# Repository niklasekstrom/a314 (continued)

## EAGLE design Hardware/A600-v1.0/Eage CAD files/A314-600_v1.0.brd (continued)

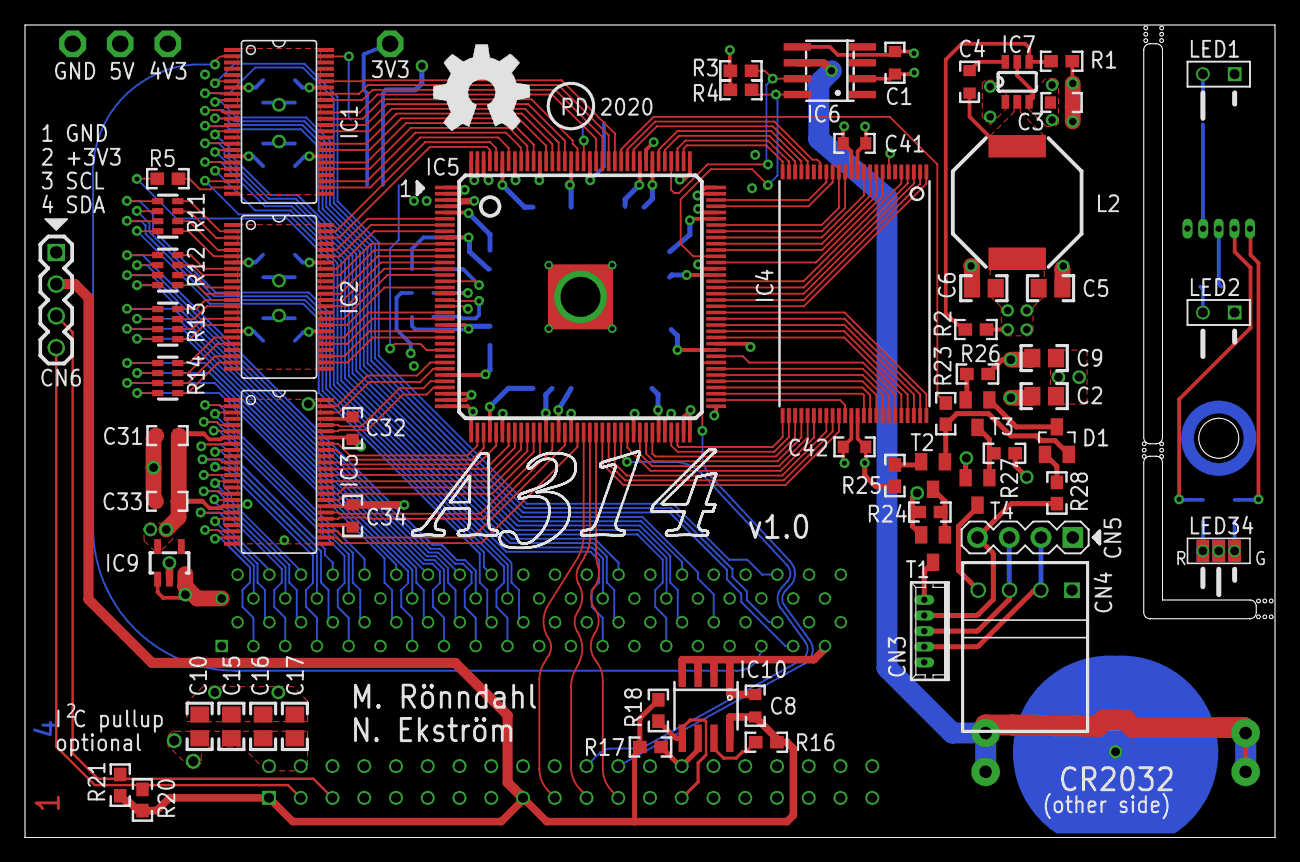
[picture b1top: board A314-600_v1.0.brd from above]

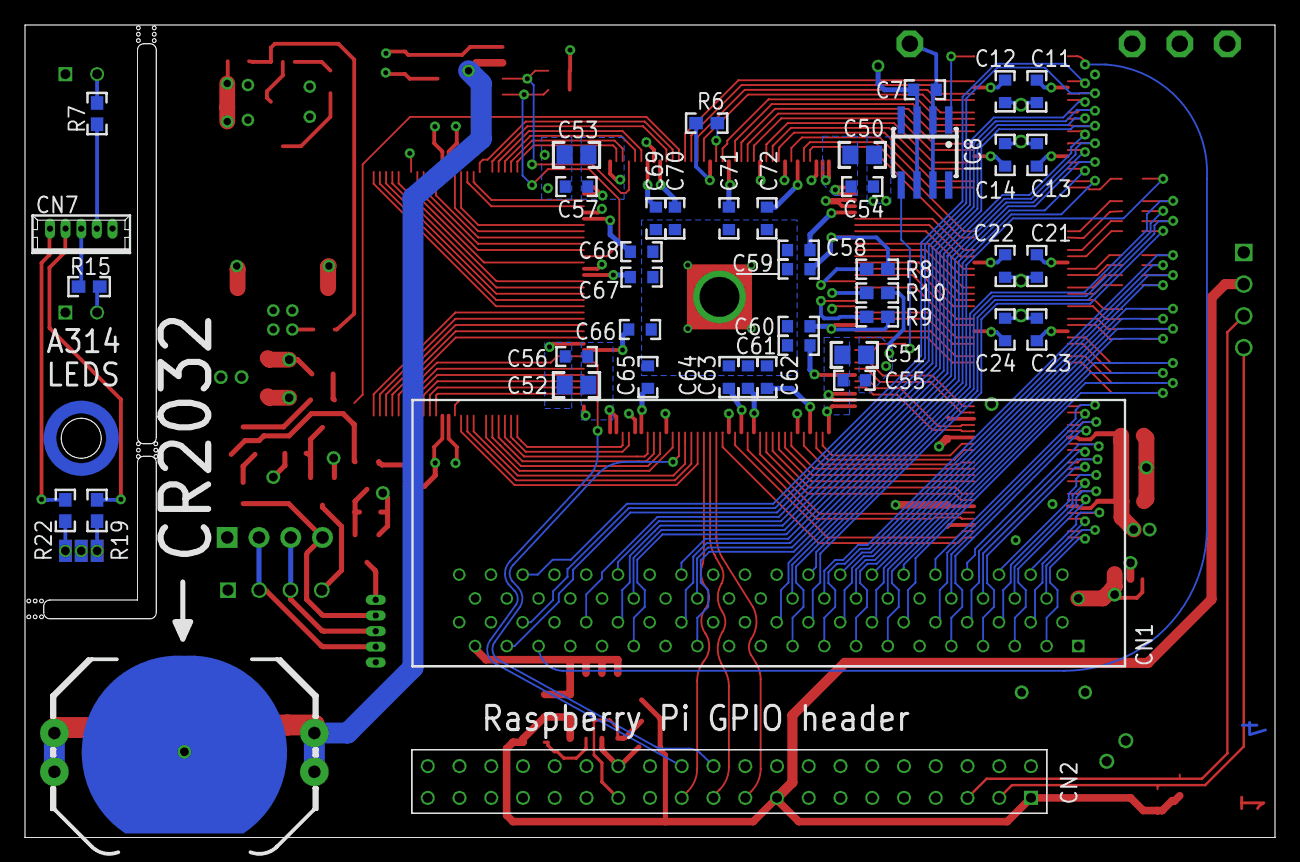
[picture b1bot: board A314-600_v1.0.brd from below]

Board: 4 copper layers, 100.0 x 65.0 mm, 111 parts (43 on the bottom side), 197 nets.

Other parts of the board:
U$1: OSHW_8_NOTEXT
U$2: A314_LOGO

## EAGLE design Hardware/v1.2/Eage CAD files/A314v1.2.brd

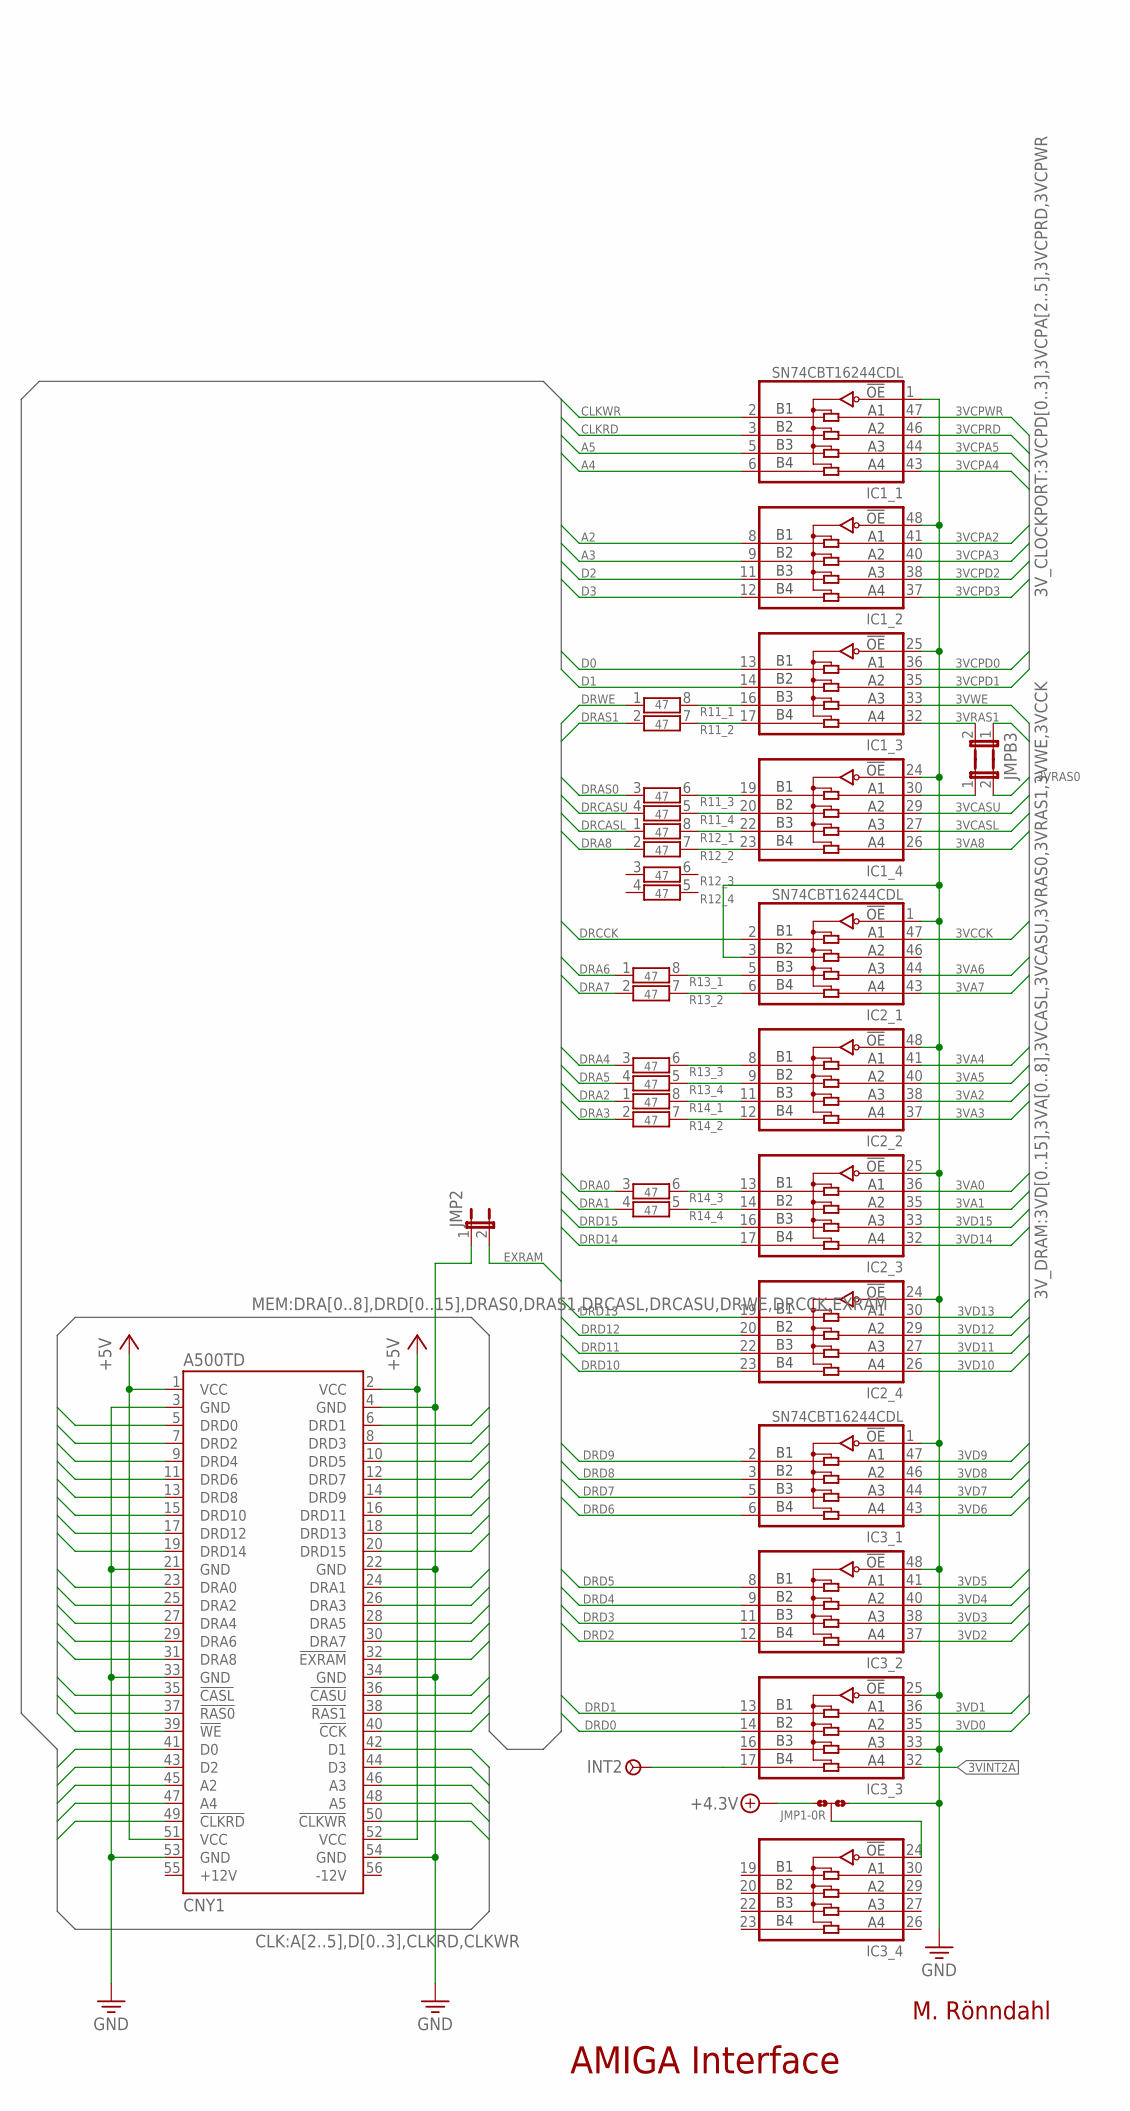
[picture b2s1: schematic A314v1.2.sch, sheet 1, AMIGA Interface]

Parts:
CNY1: A500TD; TRAPDOOR
IC1, IC2, IC3: SN74CBT16244CDL; SSOP-DL48
INT2: TP1; P1-08
JMP1: 0R-JUMPC; C0R-JMP
JMP2: JP1E; JP1
JMP3: RAS0; JP1
JMPB3: JP1E; JP1
R11, R12, R13, R14: 47; CTS742C083

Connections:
3VA0: IC2.36 (A1); also elsewhere on the board
3VA1: IC2.35 (A2); also elsewhere on the board
3VA2: IC2.38 (A3); also elsewhere on the board
3VA3: IC2.37 (A4); also elsewhere on the board
3VA4: IC2.41 (A1); also elsewhere on the board
3VA5: IC2.40 (A2); also elsewhere on the board
3VA6: IC2.44 (A3); also elsewhere on the board
3VA7: IC2.43 (A4); also elsewhere on the board
3VA8: IC1.26 (A4); also elsewhere on the board
3VCASL: IC1.27 (A3); also elsewhere on the board
3VCASU: IC1.29 (A2); also elsewhere on the board
3VCCK: IC2.47 (A1); also elsewhere on the board
3VCPA2: IC1.41 (A1); also elsewhere on the board
3VCPA3: IC1.40 (A2); also elsewhere on the board
3VCPA4: IC1.43 (A4); also elsewhere on the board
3VCPA5: IC1.44 (A3); also elsewhere on the board
3VCPD0: IC1.36 (A1); also elsewhere on the board
3VCPD1: IC1.35 (A2); also elsewhere on the board
3VCPD2: IC1.38 (A3); also elsewhere on the board
3VCPD3: IC1.37 (A4); also elsewhere on the board
3VCPRD: IC1.46 (A2); also elsewhere on the board
3VCPWR: IC1.47 (A1); also elsewhere on the board
3VD0: IC3.35 (A2); also elsewhere on the board
3VD1: IC3.36 (A1); also elsewhere on the board
3VD2: IC3.37 (A4); also elsewhere on the board
3VD3: IC3.38 (A3); also elsewhere on the board
3VD4: IC3.40 (A2); also elsewhere on the board
3VD5: IC3.41 (A1); also elsewhere on the board
3VD6: IC3.43 (A4); also elsewhere on the board
3VD7: IC3.44 (A3); also elsewhere on the board
3VD8: IC3.46 (A2); also elsewhere on the board
3VD9: IC3.47 (A1); also elsewhere on the board
3VD10: IC2.26 (A4); also elsewhere on the board
3VD11: IC2.27 (A3); also elsewhere on the board
3VD12: IC2.29 (A2); also elsewhere on the board
3VD13: IC2.30 (A1); also elsewhere on the board
3VD14: IC2.32 (A4); also elsewhere on the board
3VD15: IC2.33 (A3); also elsewhere on the board
3VINT2A: IC3.32 (A4); also elsewhere on the board
3VRAS0: JMP3.2; also elsewhere on the board
3VRAS1: JMPB3.1; also elsewhere on the board
3VWE: IC1.33 (A3); also elsewhere on the board
+4.3V: JMP1.1; also elsewhere on the board
+5V: CNY1.1 (VCC), CNY1.2 (VCC), CNY1.51 (VCC), CNY1.52 (VCC); also elsewhere on the board
A2: CNY1.45 (A2), IC1.8 (B1)
A3: CNY1.46 (A3), IC1.9 (B2)
A4: CNY1.47 (A4), IC1.6 (B4)
A5: CNY1.48 (A5), IC1.5 (B3)
CLKRD: CNY1.49 (!CLKRD), IC1.3 (B2)
CLKWR: CNY1.50 (!CLKWR), IC1.2 (B1)
D0: CNY1.41 (D0), IC1.13 (B1)
D1: CNY1.42 (D1), IC1.14 (B2)
D2: CNY1.43 (D2), IC1.11 (B3)
D3: CNY1.44 (D3), IC1.12 (B4)
DRA0: CNY1.23 (DRA0), R14.3
DRA1: CNY1.24 (DRA1), R14.4
DRA2: CNY1.25 (DRA2), R14.1
DRA3: CNY1.26 (DRA3), R14.2
DRA4: CNY1.27 (DRA4), R13.3
DRA5: CNY1.28 (DRA5), R13.4
DRA6: CNY1.29 (DRA6), R13.1
DRA7: CNY1.30 (DRA7), R13.2
DRA8: CNY1.31 (DRA8), R12.2
DRA8_L: IC1.23 (B4), R12.7
DRAS0: CNY1.37 (!RAS0), R11.3
DRAS0_L: IC1.19 (B1), R11.6
DRAS1: CNY1.38 (!RAS1), R11.2
DRAS1_L: IC1.17 (B4), R11.7
DRCASL: CNY1.35 (!CASL), R12.1
DRCASL_L: IC1.22 (B3), R12.8
DRCASU: CNY1.36 (!CASU), R11.4
DRCASU_L: IC1.20 (B2), R11.5
DRCCK: CNY1.40 (!CCK), IC2.2 (B1)
DRD0: CNY1.5 (DRD0), IC3.14 (B2)
DRD1: CNY1.6 (DRD1), IC3.13 (B1)
DRD2: CNY1.7 (DRD2), IC3.12 (B4)
DRD3: CNY1.8 (DRD3), IC3.11 (B3)
DRD4: CNY1.9 (DRD4), IC3.9 (B2)
DRD5: CNY1.10 (DRD5), IC3.8 (B1)
DRD6: CNY1.11 (DRD6), IC3.6 (B4)
DRD7: CNY1.12 (DRD7), IC3.5 (B3)
DRD8: CNY1.13 (DRD8), IC3.3 (B2)
DRD9: CNY1.14 (DRD9), IC3.2 (B1)
DRD10: CNY1.15 (DRD10), IC2.23 (B4)
DRD11: CNY1.16 (DRD11), IC2.22 (B3)
DRD12: CNY1.17 (DRD12), IC2.20 (B2)
DRD13: CNY1.18 (DRD13), IC2.19 (B1)
DRD14: CNY1.19 (DRD14), IC2.17 (B4)
DRD15: CNY1.20 (DRD15), IC2.16 (B3)
DRWE: CNY1.39 (!WE), R11.1
DRWE_L: IC1.16 (B3), R11.8
EXRAM: CNY1.32 (!EXRAM), JMP2.2
GND: CNY1.3 (GND), CNY1.4 (GND), CNY1.21 (GND), CNY1.22 (GND), CNY1.33 (GND), CNY1.34 (GND), CNY1.53 (GND), CNY1.54 (GND), IC1.1 (!OE), IC1.24 (!OE), IC1.25 (!OE), IC1.48 (!OE), IC2.1 (!OE), IC2.3 (B2), IC2.24 (!OE), IC2.25 (!OE), IC2.48 (!OE), IC3.1 (!OE), IC3.25 (!OE), IC3.33 (A3), IC3.48 (!OE), JMP1.3, JMP2.1; also elsewhere on the board
INT2A: IC3.17 (B4), INT2.TP
unnamed: IC2.14 (B2), R14.5
unnamed: IC2.13 (B1), R14.6
unnamed: IC2.12 (B4), R14.7
unnamed: IC2.11 (B3), R14.8
unnamed: IC2.9 (B2), R13.5
unnamed: IC2.8 (B1), R13.6
unnamed: IC2.6 (B4), R13.7
unnamed: IC2.5 (B3), R13.8
OUTPUT_EN: IC3.24 (!OE), JMP1.2
RAS0: IC1.30 (A1), JMP3.1
RAS1: IC1.32 (A4), JMPB3.2

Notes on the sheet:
AMIGA Interface
M. Rönndahl

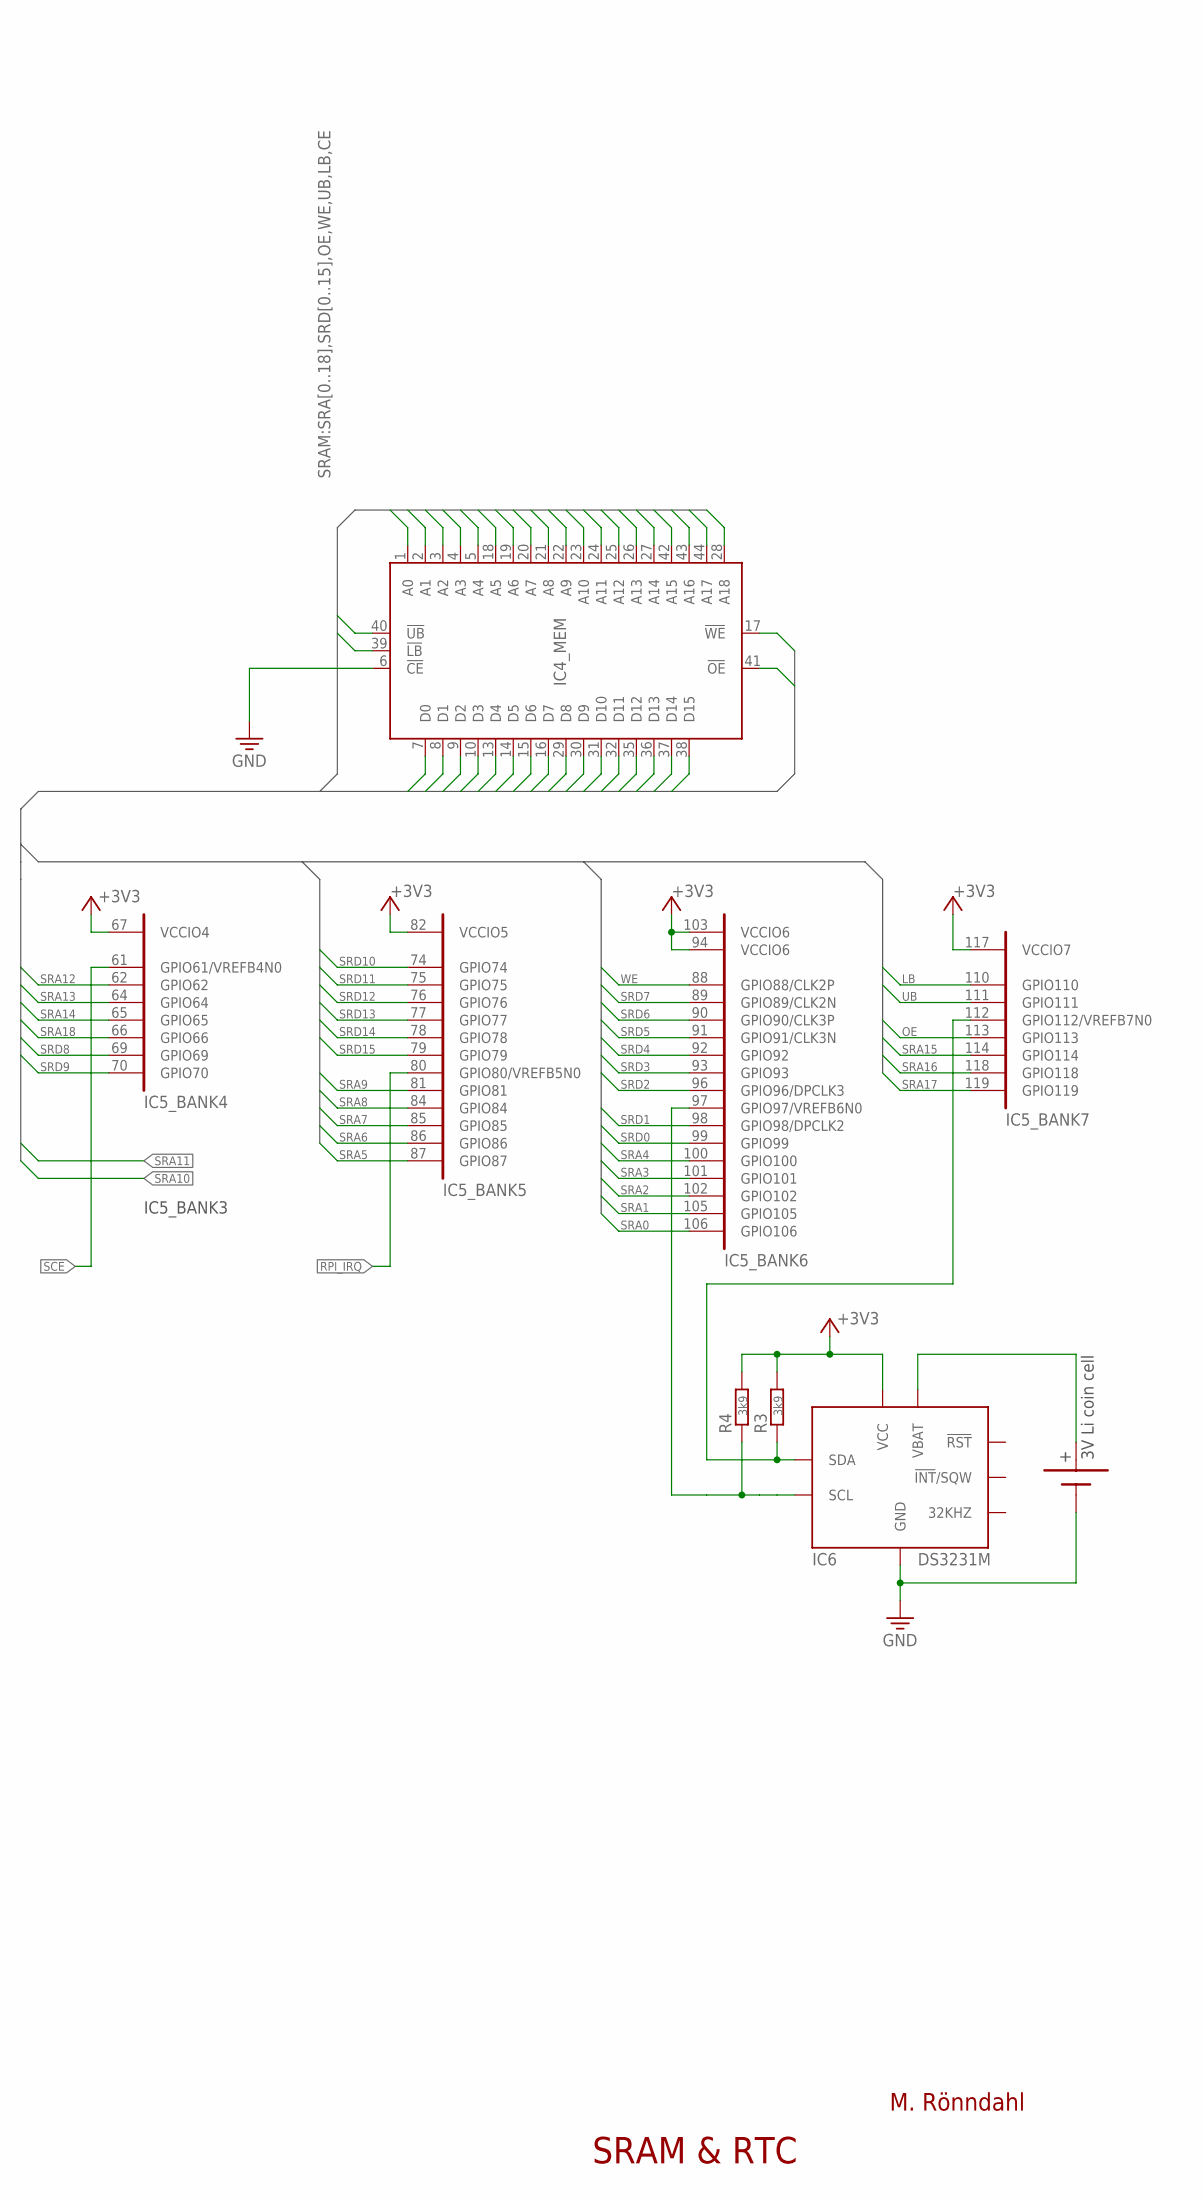
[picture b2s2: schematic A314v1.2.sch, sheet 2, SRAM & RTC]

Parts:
BAT1: CR2025/CR2032TH; LINX20XX-THM
IC4: IS61WV51216BLL-10TLI; TSOP-2
IC5: 10M08SCE144; SQFP-S-20X20-144
IC6: DS3231M; SOIC8
R3, R4: 3k9; R0805

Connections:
+: BAT1.+@1 (+), BAT1.+@2 (+), BAT1.+@3 (+), BAT1.+@4 (+), IC6.6 (VBAT)
+3V3: IC5.67 (VCCIO4), IC5.82 (VCCIO5), IC5.94 (VCCIO6), IC5.103 (VCCIO6), IC5.117 (VCCIO7), IC6.2 (VCC), R3.2, R4.2; also elsewhere on the board
GND: BAT1.GND (-), IC4.6 (!CE), IC6.5 (GND); also elsewhere on the board
LB: IC4.39 (!LB), IC5.110 (GPIO110)
OE: IC4.41 (!OE), IC5.113 (GPIO113)
RPI_IRQ: IC5.80 (GPIO80/VREFB5N0); also elsewhere on the board
SCE: IC5.61 (GPIO61/VREFB4N0); also elsewhere on the board
SCL: IC5.97 (GPIO97/VREFB6N0), IC6.8 (SCL), R4.1
SDA: IC5.112 (GPIO112/VREFB7N0), IC6.7 (SDA), R3.1
SRA0: IC4.1 (A0), IC5.106 (GPIO106)
SRA1: IC4.2 (A1), IC5.105 (GPIO105)
SRA2: IC4.3 (A2), IC5.102 (GPIO102)
SRA3: IC4.4 (A3), IC5.101 (GPIO101)
SRA4: IC4.5 (A4), IC5.100 (GPIO100)
SRA5: IC4.18 (A5), IC5.87 (GPIO87)
SRA6: IC4.19 (A6), IC5.86 (GPIO86)
SRA7: IC4.20 (A7), IC5.85 (GPIO85)
SRA8: IC4.21 (A8), IC5.84 (GPIO84)
SRA9: IC4.22 (A9), IC5.81 (GPIO81)
SRA10: IC4.23 (A10); also elsewhere on the board
SRA11: IC4.24 (A11); also elsewhere on the board
SRA12: IC4.25 (A12), IC5.62 (GPIO62)
SRA13: IC4.26 (A13), IC5.64 (GPIO64)
SRA14: IC4.27 (A14), IC5.65 (GPIO65)
SRA15: IC4.42 (A15), IC5.114 (GPIO114)
SRA16: IC4.43 (A16), IC5.118 (GPIO118)
SRA17: IC4.44 (A17), IC5.119 (GPIO119)
SRA18: IC4.28 (A18), IC5.66 (GPIO66)
SRD0: IC4.7 (D0), IC5.99 (GPIO99)
SRD1: IC4.8 (D1), IC5.98 (GPIO98/DPCLK2)
SRD2: IC4.9 (D2), IC5.96 (GPIO96/DPCLK3)
SRD3: IC4.10 (D3), IC5.93 (GPIO93)
SRD4: IC4.13 (D4), IC5.92 (GPIO92)
SRD5: IC4.14 (D5), IC5.91 (GPIO91/CLK3N)
SRD6: IC4.15 (D6), IC5.90 (GPIO90/CLK3P)
SRD7: IC4.16 (D7), IC5.89 (GPIO89/CLK2N)
SRD8: IC4.29 (D8), IC5.69 (GPIO69)
SRD9: IC4.30 (D9), IC5.70 (GPIO70)
SRD10: IC4.31 (D10), IC5.74 (GPIO74)
SRD11: IC4.32 (D11), IC5.75 (GPIO75)
SRD12: IC4.35 (D12), IC5.76 (GPIO76)
SRD13: IC4.36 (D13), IC5.77 (GPIO77)
SRD14: IC4.37 (D14), IC5.78 (GPIO78)
SRD15: IC4.38 (D15), IC5.79 (GPIO79)
UB: IC4.40 (!UB), IC5.111 (GPIO111)
WE: IC4.17 (!WE), IC5.88 (GPIO88/CLK2P)

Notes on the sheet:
IC5_BANK3
SRAM & RTC
3V Li coin cell
M. Rönndahl

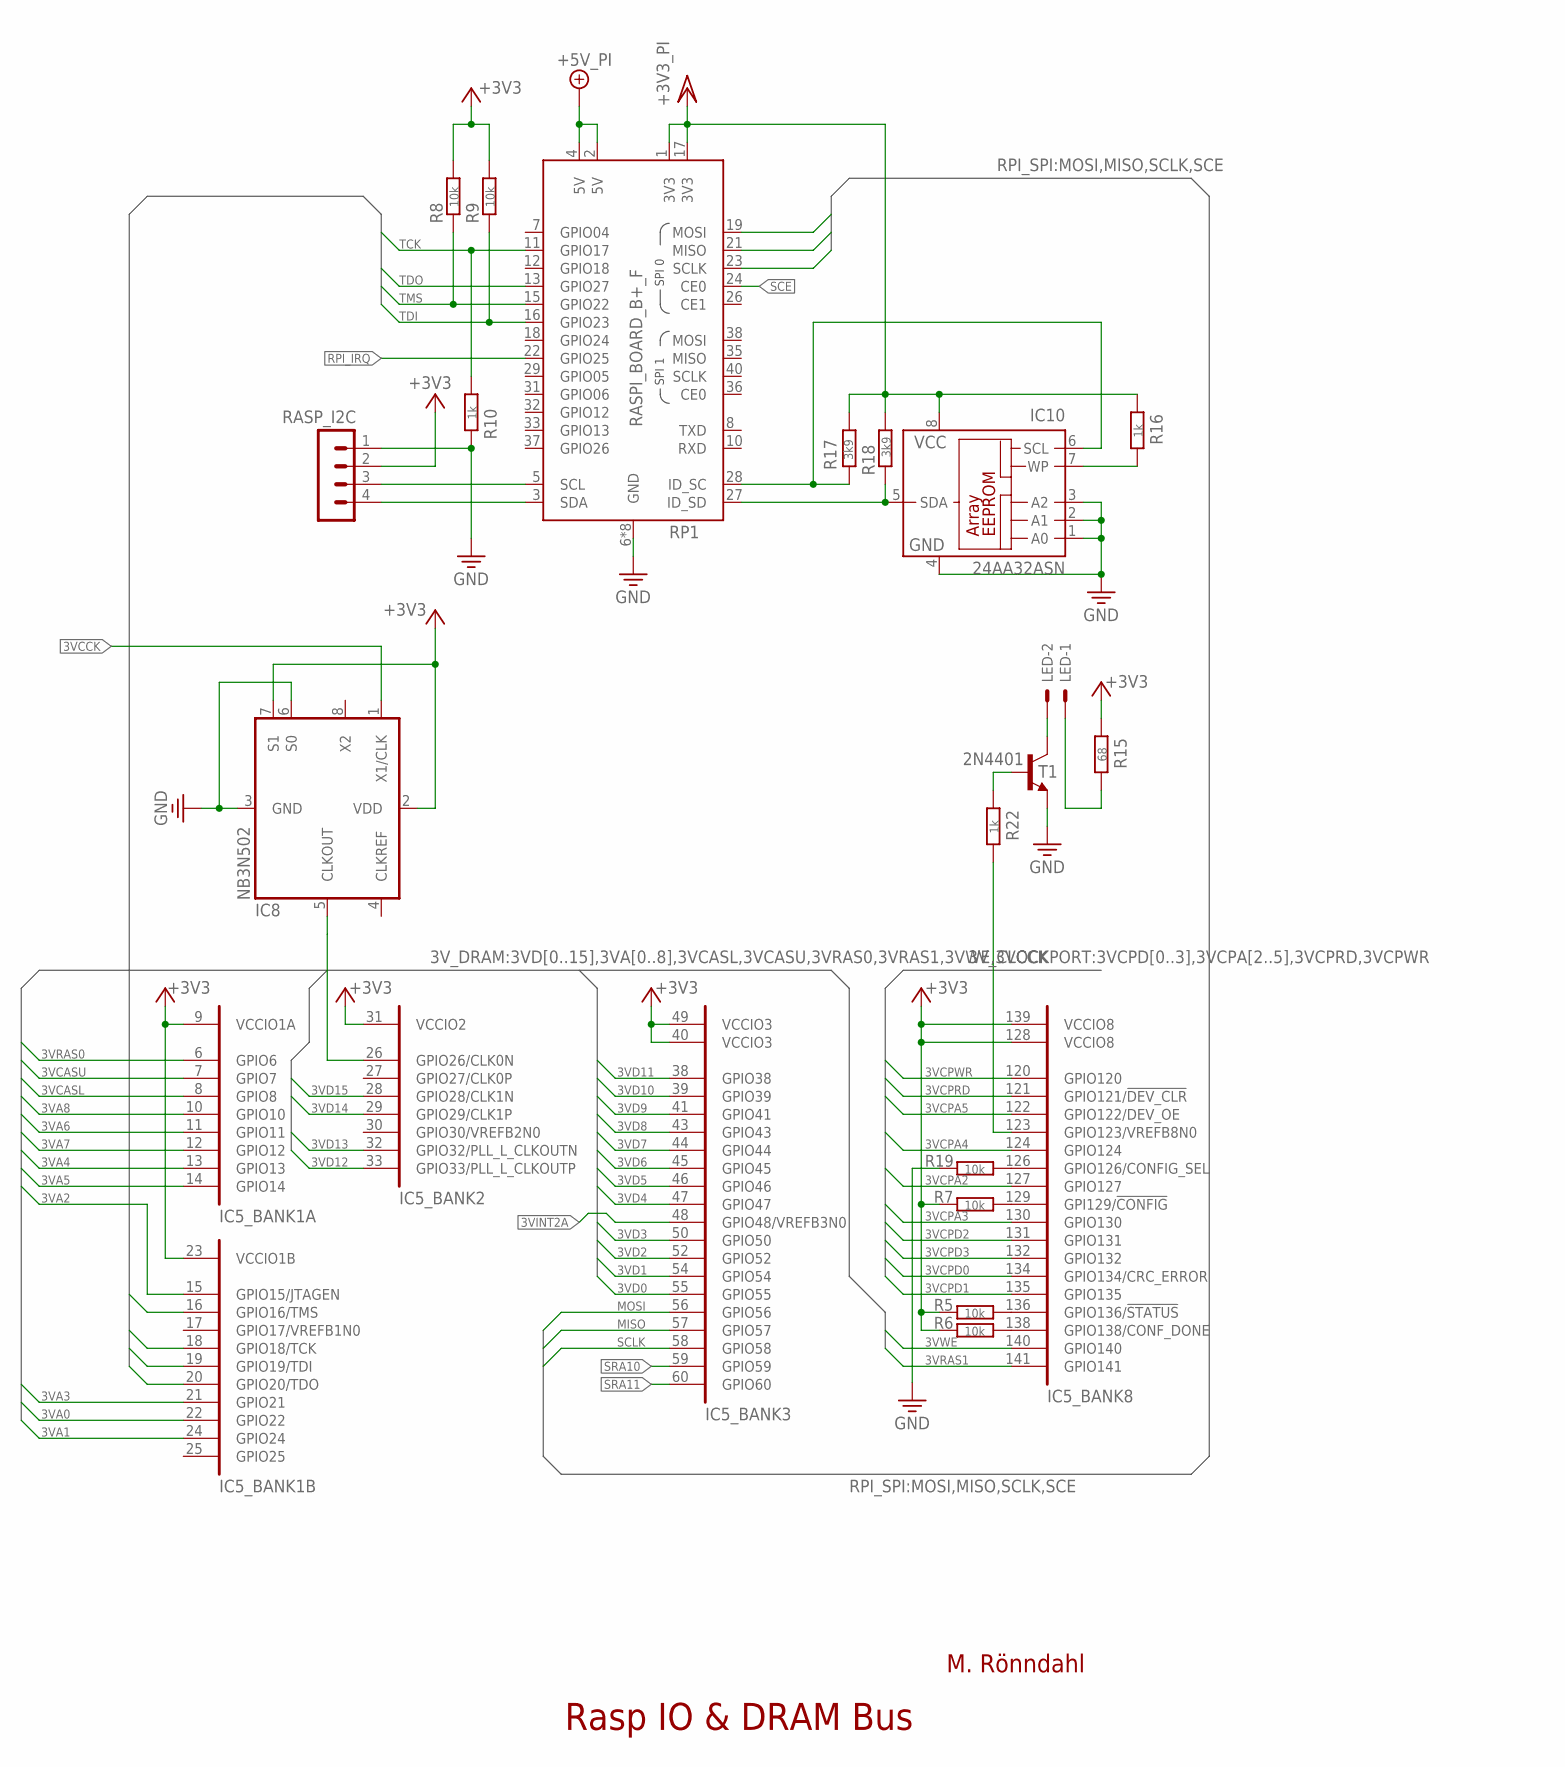
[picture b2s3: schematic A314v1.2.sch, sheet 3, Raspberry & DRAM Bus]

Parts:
IC5: 10M08SCE144; SQFP-S-20X20-144
IC8: NB3N502; SO08
IC10: 24AA32ASN; SO-08
LED: 22-23-2021
R5, R6, R7, R8, R9, R19: 10k; R0805
R10, R16, R22: 1k; R0805
R15: 68; R0805
R17, R18: 3k9; R0805
RASP_I2C: MA04-1
RP1: RASPI_BOARD_B+_F; RASPI_BOARD_B+_FULL
T1: 2N4401; SOT23-BEC

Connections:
3VA0: IC5.22 (GPIO22); also elsewhere on the board
3VA1: IC5.24 (GPIO24); also elsewhere on the board
3VA2: IC5.15 (GPIO15/JTAGEN); also elsewhere on the board
3VA3: IC5.21 (GPIO21); also elsewhere on the board
3VA4: IC5.13 (GPIO13); also elsewhere on the board
3VA5: IC5.14 (GPIO14); also elsewhere on the board
3VA6: IC5.11 (GPIO11); also elsewhere on the board
3VA7: IC5.12 (GPIO12); also elsewhere on the board
3VA8: IC5.10 (GPIO10); also elsewhere on the board
3VCASL: IC5.8 (GPIO8); also elsewhere on the board
3VCASU: IC5.7 (GPIO7); also elsewhere on the board
3VCCK: IC8.1 (X1/CLK); also elsewhere on the board
3VCPA2: IC5.127 (GPIO127); also elsewhere on the board
3VCPA3: IC5.130 (GPIO130); also elsewhere on the board
3VCPA4: IC5.124 (GPIO124); also elsewhere on the board
3VCPA5: IC5.122 (GPIO122/DEV_OE); also elsewhere on the board
3VCPD0: IC5.134 (GPIO134/CRC_ERROR); also elsewhere on the board
3VCPD1: IC5.135 (GPIO135); also elsewhere on the board
3VCPD2: IC5.131 (GPIO131); also elsewhere on the board
3VCPD3: IC5.132 (GPIO132); also elsewhere on the board
3VCPRD: IC5.121 (GPIO121/!DEV_CLR); also elsewhere on the board
3VCPWR: IC5.120 (GPIO120); also elsewhere on the board
3VD0: IC5.55 (GPIO55); also elsewhere on the board
3VD1: IC5.54 (GPIO54); also elsewhere on the board
3VD2: IC5.52 (GPIO52); also elsewhere on the board
3VD3: IC5.50 (GPIO50); also elsewhere on the board
3VD4: IC5.47 (GPIO47); also elsewhere on the board
3VD5: IC5.46 (GPIO46); also elsewhere on the board
3VD6: IC5.45 (GPIO45); also elsewhere on the board
3VD7: IC5.44 (GPIO44); also elsewhere on the board
3VD8: IC5.43 (GPIO43); also elsewhere on the board
3VD9: IC5.41 (GPIO41); also elsewhere on the board
3VD10: IC5.39 (GPIO39); also elsewhere on the board
3VD11: IC5.38 (GPIO38); also elsewhere on the board
3VD12: IC5.33 (GPIO33/PLL_L_CLKOUTP); also elsewhere on the board
3VD13: IC5.32 (GPIO32/PLL_L_CLKOUTN); also elsewhere on the board
3VD14: IC5.29 (GPIO29/CLK1P); also elsewhere on the board
3VD15: IC5.28 (GPIO28/CLK1N); also elsewhere on the board
3VINT2A: IC5.48 (GPIO48/VREFB3N0); also elsewhere on the board
3VRAS0: IC5.6 (GPIO6); also elsewhere on the board
3VRAS1: IC5.141 (GPIO141); also elsewhere on the board
3VWE: IC5.140 (GPIO140); also elsewhere on the board
14MHZ: IC5.26 (GPIO26/CLK0N), IC8.5 (CLKOUT)
!CFG: IC5.129 (GPI129/!CONFIG), R7.2
!STAT: IC5.136 (GPIO136/!STATUS), R5.2
+3V3: IC5.9 (VCCIO1A), IC5.23 (VCCIO1B), IC5.31 (VCCIO2), IC5.40 (VCCIO3), IC5.49 (VCCIO3), IC5.128 (VCCIO8), IC5.139 (VCCIO8), IC8.2 (VDD), IC8.7 (S1), R5.1, R6.1, R7.1, R8.2, R9.2, R15.2, RASP_I2C.2; also elsewhere on the board
+5V/1: RP1.2 (5V), RP1.4 (5V); also elsewhere on the board
CFG_DNE: IC5.138 (GPIO138/CONF_DONE), R6.2
CFG_SEL: IC5.126 (GPIO126/CONFIG_SEL), R19.2
GND: IC8.3 (GND), IC8.6 (S0), IC10.1 (A0), IC10.2 (A1), IC10.3 (A2), IC10.4 (GND), R10.1, R19.1, RASP_I2C.1, RP1.6 (GND), RP1.9 (GND), RP1.14 (GND), RP1.20 (GND), RP1.25 (GND), RP1.30 (GND), RP1.34 (GND), RP1.39 (GND), T1.E; also elsewhere on the board
HAT_SCL: IC10.6 (SCL), R17.2, RP1.28 (ID_SC)
HAT_SDA: IC10.5 (SDA), R18.1, RP1.27 (ID_SD)
LED_CTRL: IC5.123 (GPIO123/VREFB8N0), R22.1
LED_PWR: LED.1, R15.1
LED_RTN: LED.2, T1.C
MISO: IC5.57 (GPIO57), RP1.21 (MISO)
MOSI: IC5.56 (GPIO56), RP1.19 (MOSI)
unnamed: R22.2, T1.B
PI_SCL: RASP_I2C.3, RP1.5 (SCL)
PI_SDA: RASP_I2C.4, RP1.3 (SDA)
RPI_IRQ: RP1.22 (GPIO25); also elsewhere on the board
SCE: RP1.24 (CE0); also elsewhere on the board
SCLK: IC5.58 (GPIO58), RP1.23 (SCLK)
SRA10: IC5.59 (GPIO59); also elsewhere on the board
SRA11: IC5.60 (GPIO60); also elsewhere on the board
TCK: IC5.18 (GPIO18/TCK), R10.2, RP1.11 (GPIO17)
TDI: IC5.19 (GPIO19/TDI), R9.1, RP1.16 (GPIO23)
TDO: IC5.20 (GPIO20/TDO), RP1.13 (GPIO27)
TMS: IC5.16 (GPIO16/TMS), R8.1, RP1.15 (GPIO22)
VCC/2: IC10.8 (VCC), R16.2, R17.1, R18.2, RP1.1 (3V3), RP1.17 (3V3); also elsewhere on the board
WP: IC10.7 (WP), R16.1

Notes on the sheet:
Rasp IO & DRAM Bus
M. Rönndahl

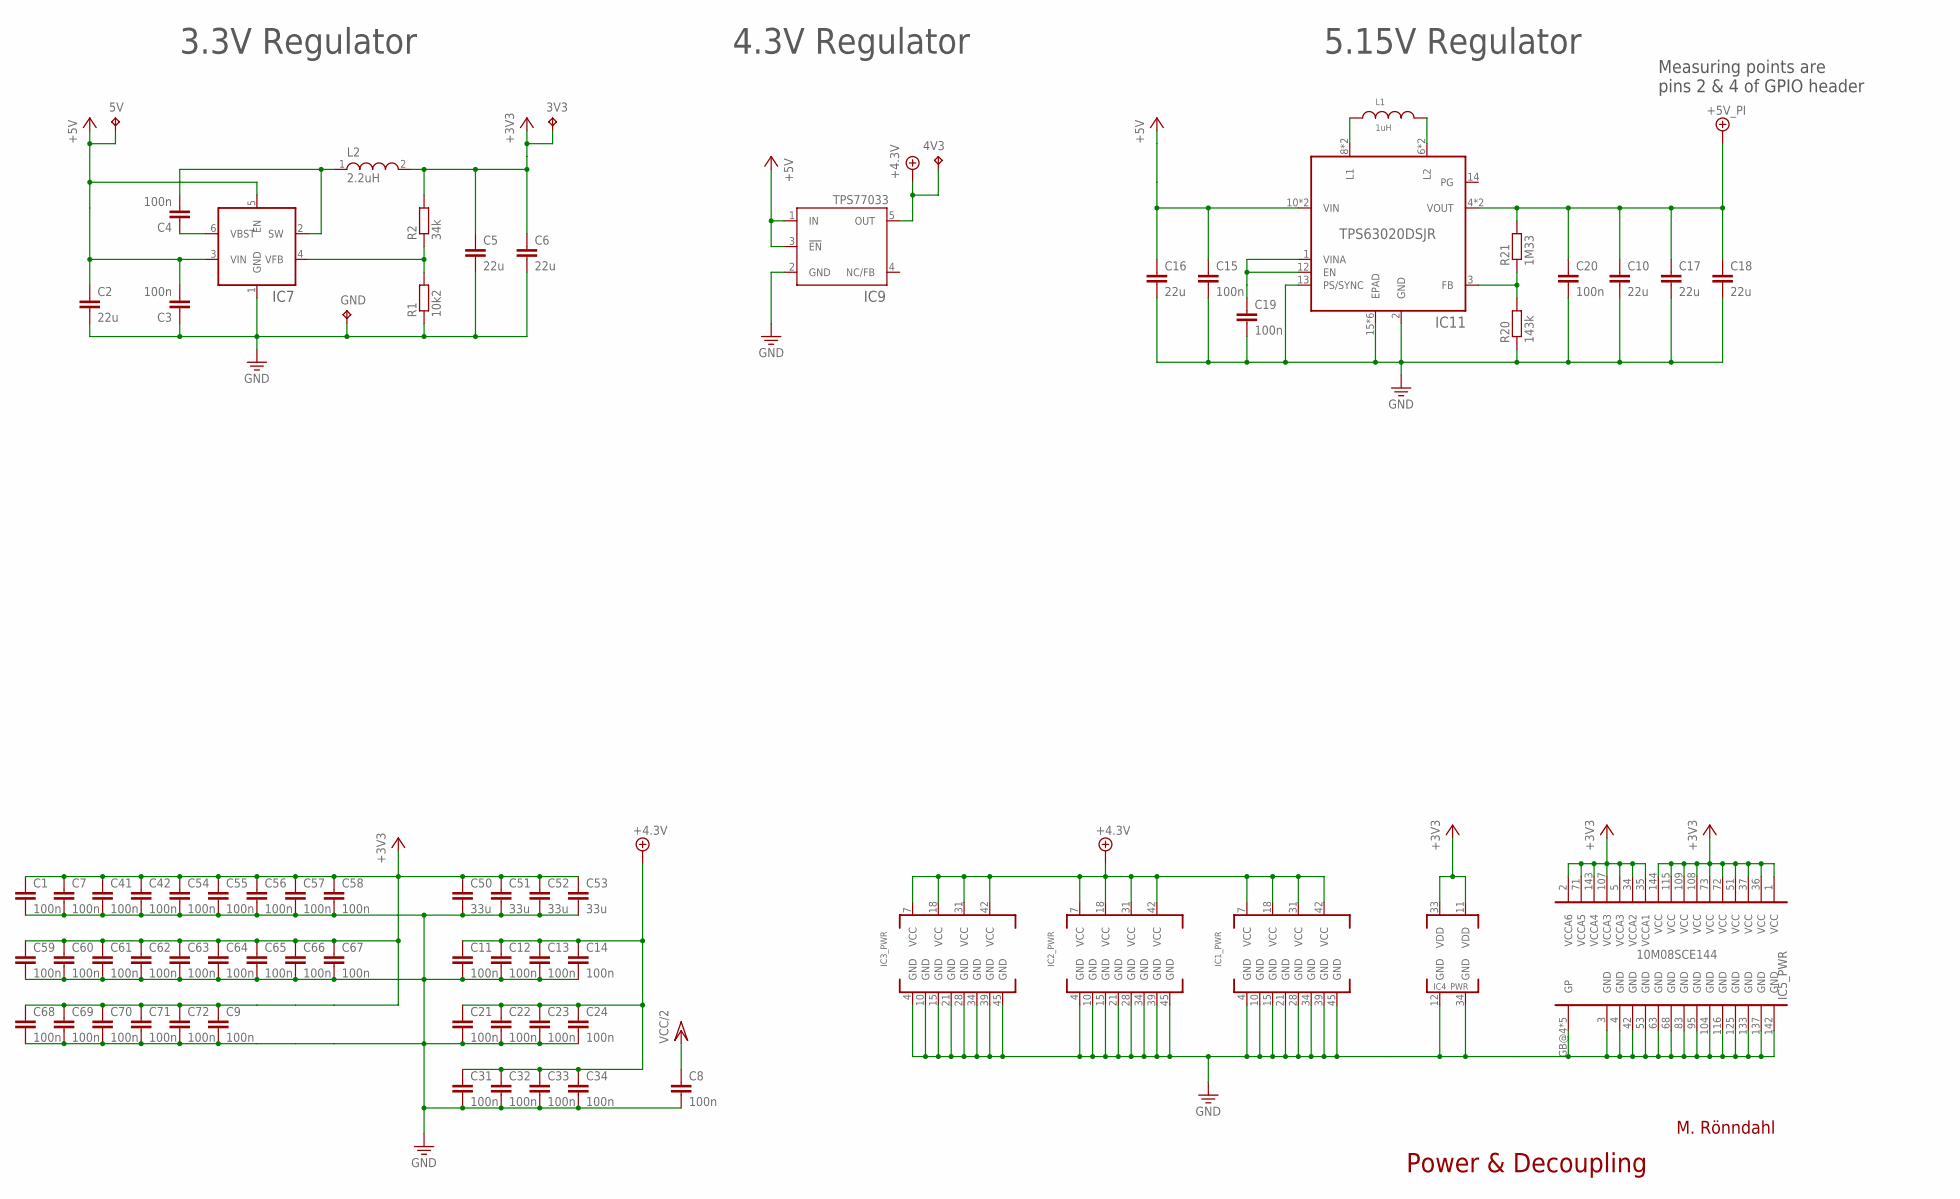
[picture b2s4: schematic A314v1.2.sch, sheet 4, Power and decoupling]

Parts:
3V3, 4V3, 5V: TPPAD1-13; P1-13
C1, C3, C4, C7, C8, C9, C11, C12, C13, C14, C15, C19, C20, C21, C22, C23, C24, C31, C32, C33, C34, C41, C42, C54, C55, C56, C57, C58, C59, C60, C61, C62, C63, C64, C65, C66, C67, C68, C69, C70, C71, C72: 100n; C0805
C2, C5, C6, C10, C16, C17, C18: 22u; C1812K; MOUSER 810-CGA8P1X7R1E226M
C50, C51, C52, C53: 33u; C0805
GND: TPPAD1-13; P1-13
IC1, IC2, IC3: SN74CBT16244CDL; SSOP-DL48
IC4: IS61WV51216BLL-10TLI; TSOP-2
IC5: 10M08SCE144; SQFP-S-20X20-144
IC7: TPS565208DDC; THIN_SO23; MOUSER 595-TPS565208DDCR
IC9: TPS77033; SOT23-DBV
IC11: TPS63020DSJR; DSJ14_2P85X1P58
L1: 1uH; WE-TPC_6823
L2: 2.2uH; WE-TPC_1028/1038; MOUSER 710-7440650022
R1: 10k2; R0805
R2: 34k; R0805
R20: 143k; R0805
R21: 1M33; R0805

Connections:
+3V3: 3V3.TP, C1.1, C5.1, C6.1, C7.1, C9.1, C41.1, C42.1, C50.1, C51.1, C52.1, C53.1, C54.1, C55.1, C56.1, C57.1, C58.1, C59.1, C60.1, C61.1, C62.1, C63.1, C64.1, C65.1, C66.1, C67.1, C68.1, C69.1, C70.1, C71.1, C72.1, IC4.11 (VDD), IC4.33 (VDD), IC5.1 (VCC), IC5.2 (VCCA6), IC5.5 (VCCA3), IC5.34 (VCCA2), IC5.35 (VCCA1), IC5.36 (VCC), IC5.37 (VCC), IC5.51 (VCC), IC5.71 (VCCA5), IC5.72 (VCC), IC5.73 (VCC), IC5.107 (VCCA3), IC5.108 (VCC), IC5.109 (VCC), IC5.115 (VCC), IC5.143 (VCCA4), IC5.144 (VCC), L2.2, R2.2; also elsewhere on the board
+4.3V: 4V3.TP, C11.1, C12.1, C13.1, C14.1, C21.1, C22.1, C23.1, C24.1, C31.1, C32.1, C33.1, C34.1, IC1.7 (VCC), IC1.18 (VCC), IC1.31 (VCC), IC1.42 (VCC), IC2.7 (VCC), IC2.18 (VCC), IC2.31 (VCC), IC2.42 (VCC), IC3.7 (VCC), IC3.18 (VCC), IC3.31 (VCC), IC3.42 (VCC), IC9.5 (OUT); also elsewhere on the board
+5V: 5V.TP, C2.1, C3.2, C15.2, C16.1, IC7.3 (VIN), IC7.5 (EN), IC9.1 (IN), IC9.3 (!EN), IC11.10 (VIN), IC11.11 (VIN); also elsewhere on the board
+5V/1: C10.1, C17.1, C18.1, C20.2, IC11.4 (VOUT), IC11.5 (VOUT), R21.2; also elsewhere on the board
BST1: C4.1, IC7.6 (VBST)
FB1: IC7.4 (VFB), R1.2, R2.1
FB2: IC11.3 (FB), R20.2, R21.1
GND: C1.2, C2.2, C3.1, C5.2, C6.2, C7.2, C8.2, C9.2, C10.2, C11.2, C12.2, C13.2, C14.2, C15.1, C16.2, C17.2, C18.2, C19.1, C20.1, C21.2, C22.2, C23.2, C24.2, C31.2, C32.2, C33.2, C34.2, C41.2, C42.2, C50.2, C51.2, C52.2, C53.2, C54.2, C55.2, C56.2, C57.2, C58.2, C59.2, C60.2, C61.2, C62.2, C63.2, C64.2, C65.2, C66.2, C67.2, C68.2, C69.2, C70.2, C71.2, C72.2, GND.TP, IC1.4 (GND), IC1.10 (GND), IC1.15 (GND), IC1.21 (GND), IC1.28 (GND), IC1.34 (GND), IC1.39 (GND), IC1.45 (GND), IC2.4 (GND), IC2.10 (GND), IC2.15 (GND), IC2.21 (GND), IC2.28 (GND), IC2.34 (GND), IC2.39 (GND), IC2.45 (GND), IC3.4 (GND), IC3.10 (GND), IC3.15 (GND), IC3.21 (GND), IC3.28 (GND), IC3.34 (GND), IC3.39 (GND), IC3.45 (GND), IC4.12 (GND), IC4.34 (GND), IC5.3 (GND), IC5.4 (GND), IC5.42 (GND), IC5.53 (GND), IC5.63 (GND), IC5.68 (GND), IC5.83 (GND), IC5.95 (GND), IC5.104 (GND), IC5.116 (GND), IC5.125 (GND), IC5.133 (GND), IC5.137 (GND), IC5.142 (GND), IC5.GB@4 (GP), IC5.GP@1 (GP), IC5.GP@2 (GP), IC5.GP@3 (GP), IC5.GP@5 (GP), IC7.1 (GND), IC9.2 (GND), IC11.2 (GND), IC11.13 (PS/SYNC), IC11.15 (EPAD), IC11.V_1 (EPAD), IC11.V_2 (EPAD), IC11.V_3 (EPAD), IC11.V_4 (EPAD), IC11.V_5 (EPAD), R1.1, R20.1; also elsewhere on the board
L1: IC11.8 (L1), IC11.9 (L1), L1.1
L2: IC11.6 (L2), IC11.7 (L2), L1.2
SW: C4.2, IC7.2 (SW), L2.1
VCC/2: C8.1; also elsewhere on the board
VINA: C19.2, IC11.1 (VINA), IC11.12 (EN)

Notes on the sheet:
Power & Decoupling
3.3V Regulator
4.3V Regulator
5.15V Regulator
M. Rönndahl
Measuring points are pins 2 & 4 of GPIO header
